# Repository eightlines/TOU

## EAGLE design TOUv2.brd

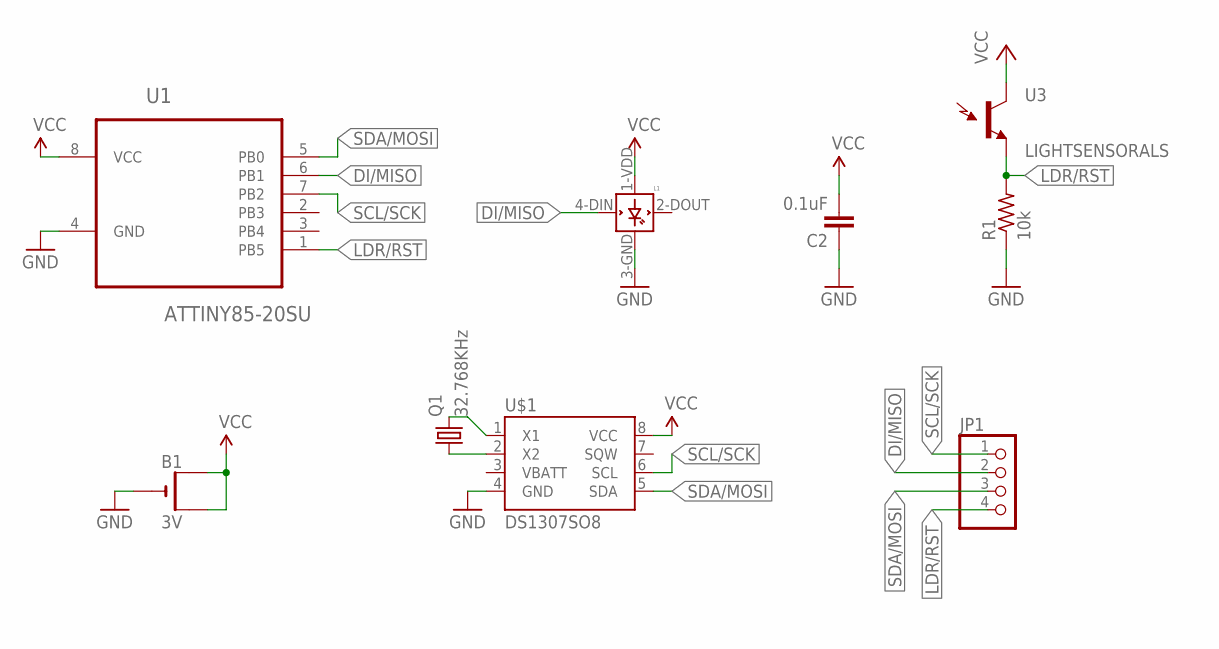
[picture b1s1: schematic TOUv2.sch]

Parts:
B1: 3V; CR2032-THRU
C2: 0.1uF; 0603-CAP
JP1: PINHD-1X4; 1X04
L1: WS2812B
Q1: 32.768KHz; CTS406
R1: 10k; R0402
U1: ATTINY85-20SU; SOIC127P798X216-8N
U3: LIGHTSENSORALS; ALS-PT19
U$1: DS1307SO8; SO08

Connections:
DI/MISO: JP1.2, L1.4-DIN (DIN), U1.6 (PB1)
GND: B1.-, C2.1, L1.3-GND (GND), R1.1, U1.4 (GND), U$1.4 (GND)
LDR/RST: JP1.4, R1.2, U1.1 (PB5), U3.E (E1)
unnamed: Q1.1, U$1.2 (X2)
unnamed: Q1.3 (2), U$1.1 (X1)
SCL/SCK: JP1.1, U1.7 (PB2), U$1.6 (SCL)
SDA/MOSI: JP1.3, U1.5 (PB0), U$1.5 (SDA)
VCC: B1.+1 (+), B1.+2 (+1), C2.2, L1.1-VDD (VDD), U1.8 (VCC), U3.C (C1), U$1.8 (VCC)

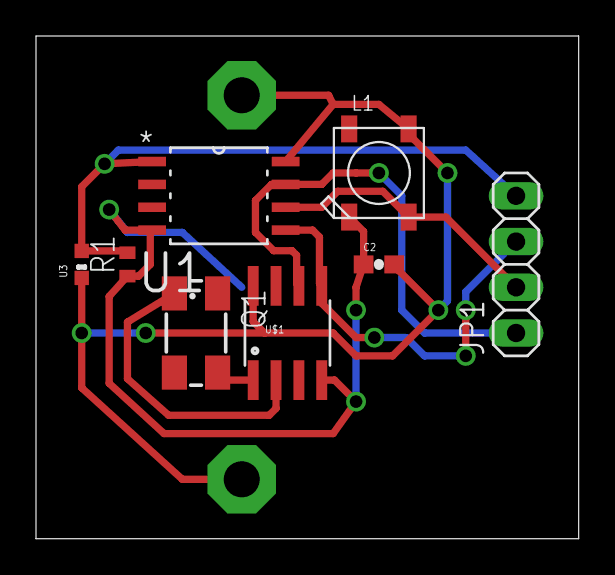
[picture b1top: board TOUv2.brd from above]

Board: 2 copper layers, 30.1 x 27.9 mm, 9 parts (1 on the bottom side), 8 nets.

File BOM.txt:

Partlist exported from TOUv2.sch at 3/6/2014 10:00 AM

Part Value          Device         Package            Description                                             MF MPN           OC_FARNELL OC_NEWARK PACKAGE PROD_ID  SUPPLIER
B1   3V             CR2032THM      CR2032-THRU                                                                                                                               
C2   0.1uF          CAP0603-CAP    0603-CAP           Capacitor                                                                                                              
JP1                 PINHD-1X4      1X04               PIN HEADER                                                                                                             
L1   WS2812B        WS2812B        WS2812B                                                                                                                                   
Q1   32.768KHz      CRYSTALCTS406  CTS406             CRYSTAL                                                                  unknown    unknown                            
R1   10k            R-US_R0402     R0402              RESISTOR, American symbol                                                                                              
U$1  DS1307SO8      DS1307SO8      SO08               I2C real-time clock with battery backup.                                                                               
U1   ATTINY85-20SU  ATTINY85-20SU  SOIC127P798X216-8N 8-bit Microcontroller with In-System Programmable Flash    ATTINY85-20SU 1455164    58M3797   SOIC-8           Atmel   
U3   LIGHTSENSORALS LIGHTSENSORALS ALS-PT19           Ambient Light Sensor                                                                                  IC-11836

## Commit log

2014-03-06 Fix CR2032 error, simplify routing, add BOM

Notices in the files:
parts and their libraries:
SparkFun-Sensors: Licensing: Creative Commons ShareAlike 4.0 International - https://creativecommons.org/licenses/by-sa/4.0
